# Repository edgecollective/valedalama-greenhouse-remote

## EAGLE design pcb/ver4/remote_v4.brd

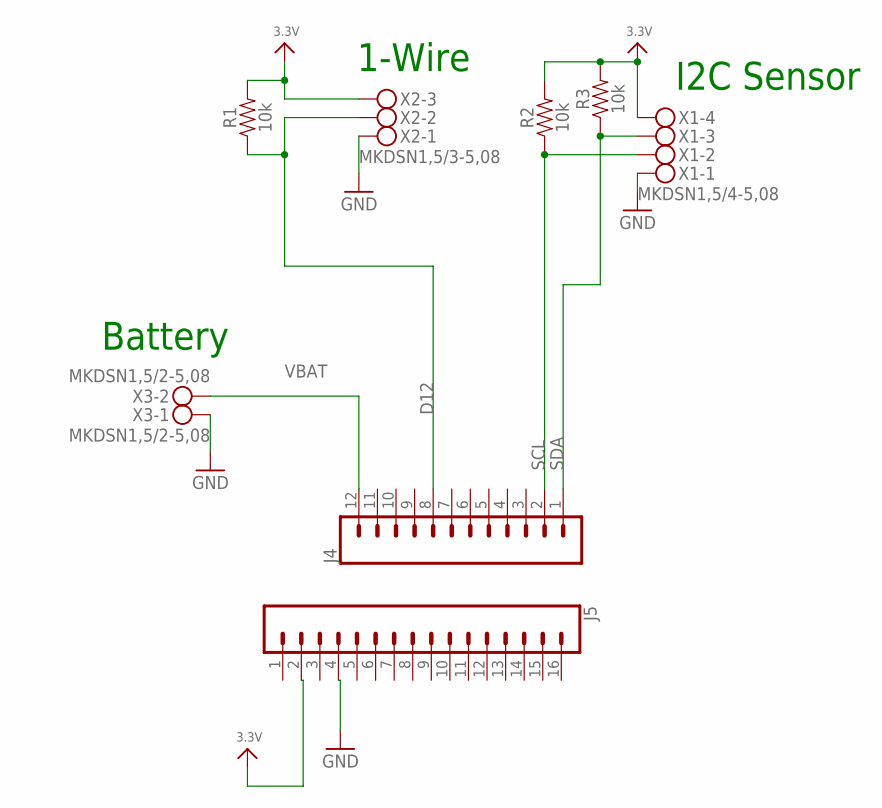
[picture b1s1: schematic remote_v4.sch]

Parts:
J4: CONN_12; 1X12
J5: CONN_16; 1X16
R1, R2, R3: 10k; AXIAL-0.3
X1: MKDSN1,5/4-5,08
X2: MKDSN1,5/3-5,08
X3: MKDSN1,5/2-5,08

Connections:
3.3V: J5.2, R1.P$2 (2), R2.P$2 (2), R3.P$2 (2), X1.4, X2.3
D12: J4.8, R1.P$1 (1), X2.2
GND: J5.4, X1.1, X2.1, X3.1
SCL: J4.2, R2.P$1 (1), X1.2
SDA: J4.1, R3.P$1 (1), X1.3
VBAT: J4.12, X3.2

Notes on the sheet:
1-Wire
I2C Sensor
Battery

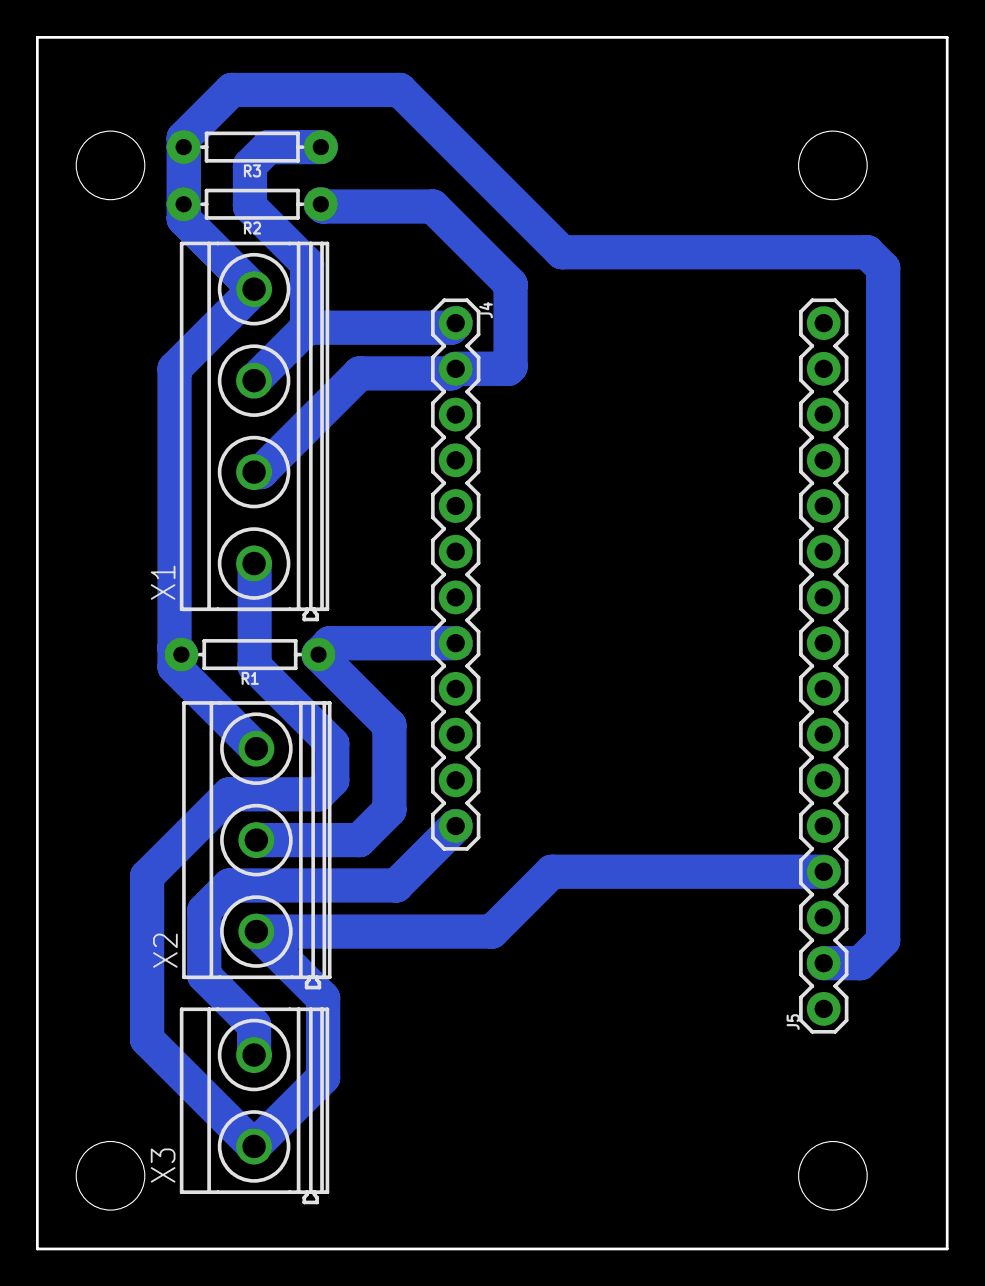
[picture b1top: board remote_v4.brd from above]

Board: 2 copper layers, 50.5 x 67.3 mm, 8 parts (0 on the bottom side), 6 nets.

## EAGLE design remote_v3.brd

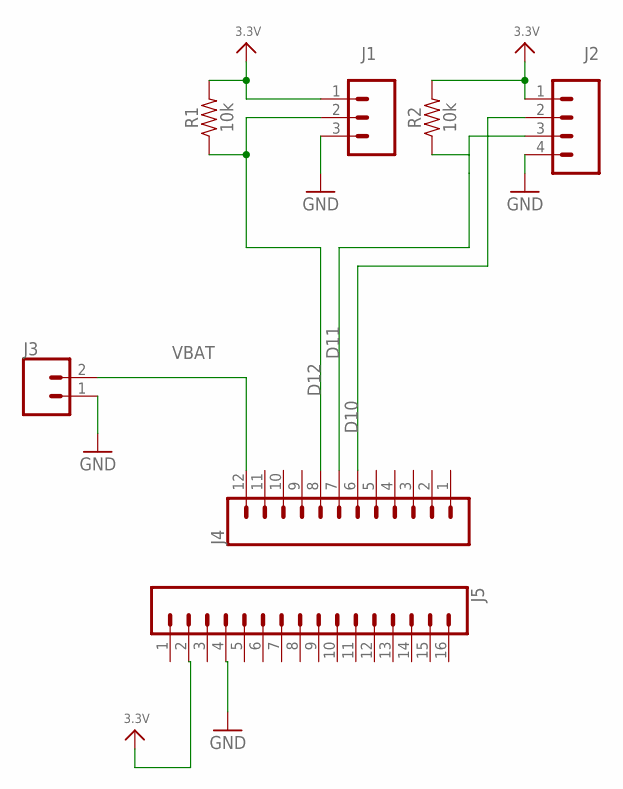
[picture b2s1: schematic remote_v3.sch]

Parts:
J1: CONN_03SCREW; SCREWTERMINAL-3.5MM-3
J2: CONN_04SCREW; SCREWTERMINAL-3.5MM-4
J3: CONN_023.5MM; SCREWTERMINAL-3.5MM-2
J4: CONN_12; 1X12
J5: CONN_16; 1X16
R1, R2: 10k; AXIAL-0.3

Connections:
3.3V: J1.1, J2.1, J5.2, R1.P$2 (2), R2.P$2 (2)
D10: J2.2, J4.6
D11: J2.3, J4.7, R2.P$1 (1)
D12: J1.2, J4.8, R1.P$1 (1)
GND: J1.3, J2.4, J3.1, J5.4
VBAT: J3.2, J4.12

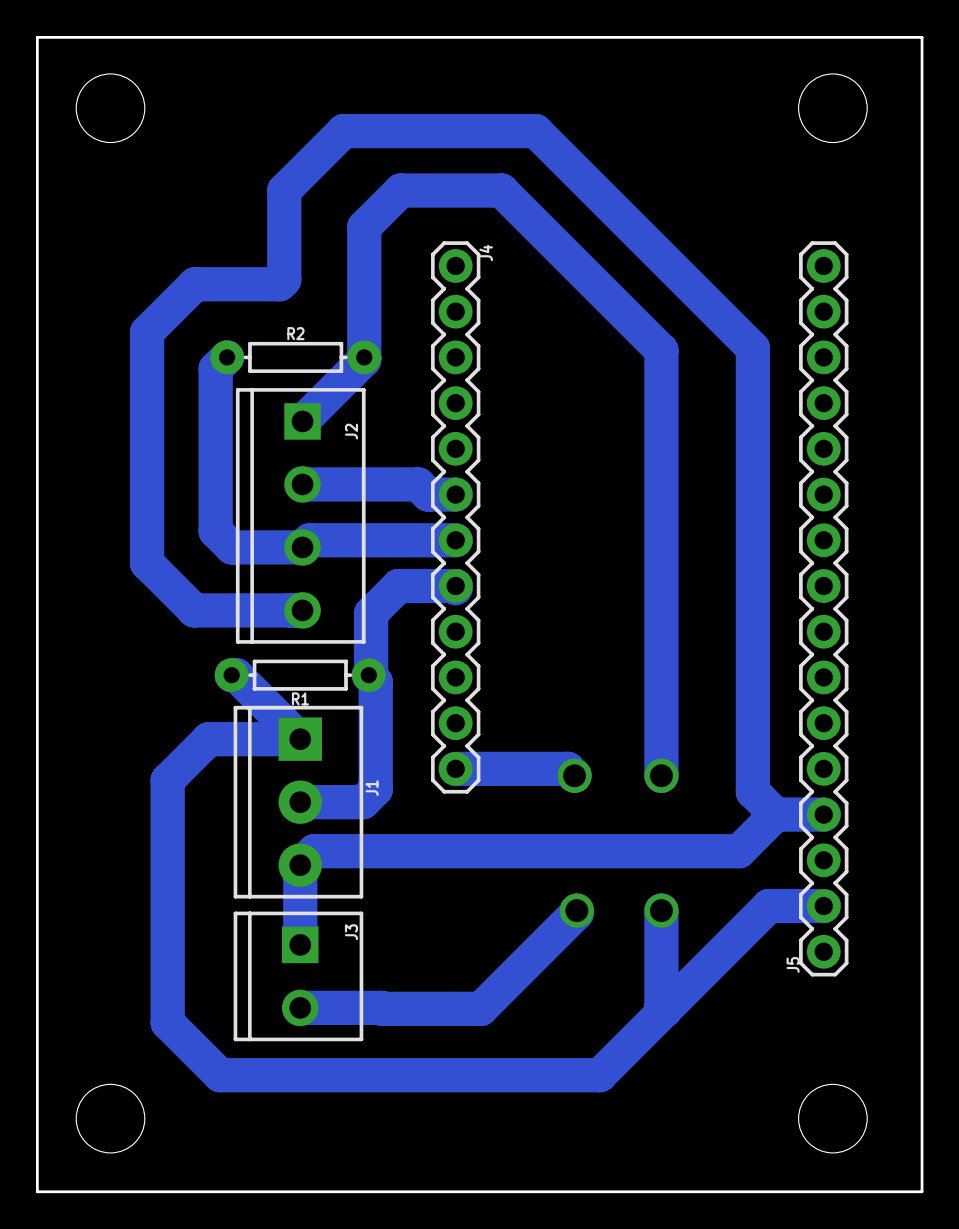
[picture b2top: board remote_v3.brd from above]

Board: 2 copper layers, 49.1 x 64.1 mm, 7 parts (0 on the bottom side), 6 nets.

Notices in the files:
parts and their libraries:
SparkFun-Connectors: Licensing: Creative Commons ShareAlike 4.0 International - https://creativecommons.org/licenses/by-sa/4.0
microbuilder: This work is placed in the public domain, and may be freely used for commercial and non-commercial work with the following conditions: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
